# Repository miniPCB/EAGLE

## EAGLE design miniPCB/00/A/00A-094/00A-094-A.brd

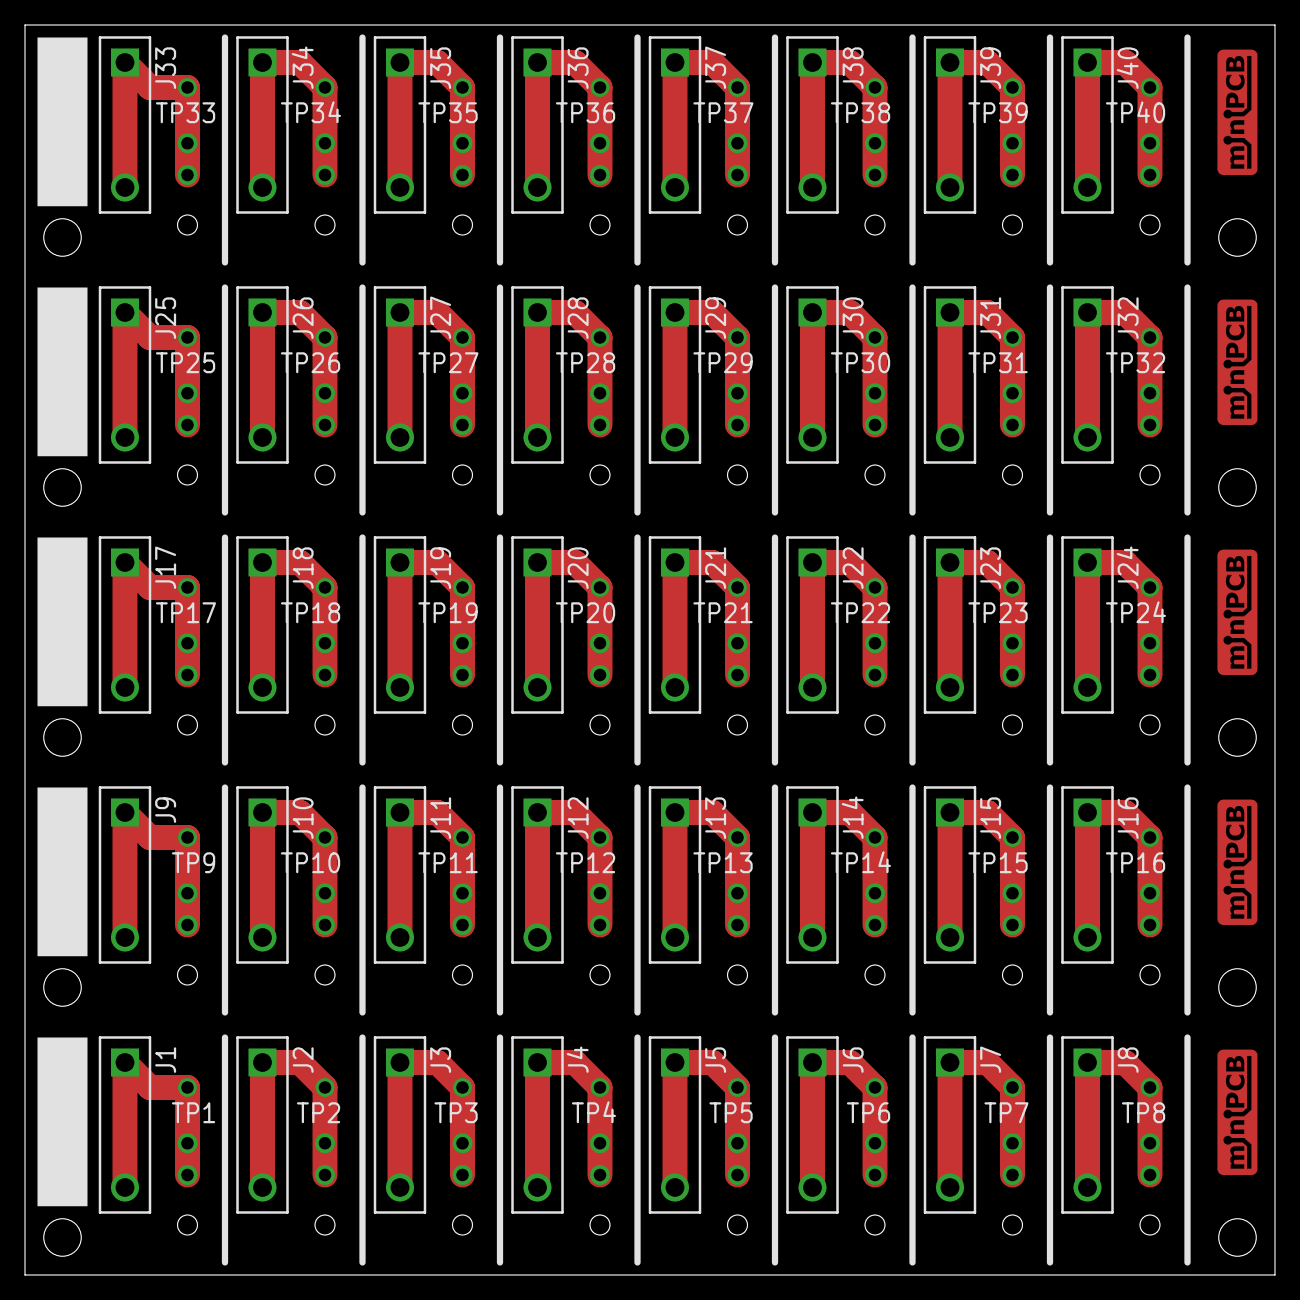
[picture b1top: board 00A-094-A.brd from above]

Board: 2 copper layers, 100.0 x 100.0 mm, 126 parts (0 on the bottom side), 40 nets.

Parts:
E$1: MINIPCB_PANEL_IMAGEFRAME
J1, J2, J3, J4, J5, J6, J7, J8, J9, J10, J11, J12, J13, J14, J15, J16, J17, J18, J19, J20, J21, J22, J23, J24, J25, J26, J27, J28, J29, J30, J31, J32, J33, J34, J35, J36, J37, J38, J39, J40: PINS_1_KE6060
P1, P2, P3, P4, P5, P6, P7, P8, P9, P10, P11, P12, P13, P14, P15, P16, P17, P18, P19, P20, P21, P22, P23, P24, P25, P26, P27, P28, P29, P30, P31, P32, P33, P34, P35, P36, P37, P38, P39, P40: PINS_1_1MM-NOTEXT
PCB1, PCB2, PCB3, PCB4, PCB5: MINIPCB_00A_20X100
TP1, TP2, TP3, TP4, TP5, TP6, TP7, TP8, TP9, TP10, TP11, TP12, TP13, TP14, TP15, TP16, TP17, TP18, TP19, TP20, TP21, TP22, TP23, TP24, TP25, TP26, TP27, TP28, TP29, TP30, TP31, TP32, TP33, TP34, TP35, TP36, TP37, TP38, TP39, TP40: PINS_1_TESTPOINT_KE5000_NOTEXT

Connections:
unnamed: J1.1, J1.2, P1.1, P1.2, TP1.1
unnamed: J8.1, J8.2, P8.1, P8.2, TP8.1
unnamed: J2.1, J2.2, P2.1, P2.2, TP2.1
unnamed: J9.1, J9.2, P9.1, P9.2, TP9.1
unnamed: J3.1, J3.2, P3.1, P3.2, TP3.1
unnamed: J10.1, J10.2, P10.1, P10.2, TP10.1
unnamed: J4.1, J4.2, P4.1, P4.2, TP4.1
unnamed: J11.1, J11.2, P11.1, P11.2, TP11.1
unnamed: J5.1, J5.2, P5.1, P5.2, TP5.1
unnamed: J12.1, J12.2, P12.1, P12.2, TP12.1
unnamed: J6.1, J6.2, P6.1, P6.2, TP6.1
unnamed: J13.1, J13.2, P13.1, P13.2, TP13.1
unnamed: J14.1, J14.2, P14.1, P14.2, TP14.1
unnamed: J7.1, J7.2, P7.1, P7.2, TP7.1
unnamed: J15.1, J15.2, P15.1, P15.2, TP15.1
unnamed: J16.1, J16.2, P16.1, P16.2, TP16.1
unnamed: J17.1, J17.2, P17.1, P17.2, TP17.1
unnamed: J18.1, J18.2, P18.1, P18.2, TP18.1
unnamed: J19.1, J19.2, P19.1, P19.2, TP19.1
unnamed: J20.1, J20.2, P20.1, P20.2, TP20.1
unnamed: J21.1, J21.2, P21.1, P21.2, TP21.1
unnamed: J22.1, J22.2, P22.1, P22.2, TP22.1
unnamed: J23.1, J23.2, P23.1, P23.2, TP23.1
unnamed: J24.1, J24.2, P24.1, P24.2, TP24.1
unnamed: J25.1, J25.2, P25.1, P25.2, TP25.1
unnamed: J26.1, J26.2, P26.1, P26.2, TP26.1
unnamed: J27.1, J27.2, P27.1, P27.2, TP27.1
unnamed: J28.1, J28.2, P28.1, P28.2, TP28.1
unnamed: J29.1, J29.2, P29.1, P29.2, TP29.1
unnamed: J30.1, J30.2, P30.1, P30.2, TP30.1
unnamed: J31.1, J31.2, P31.1, P31.2, TP31.1
unnamed: J32.1, J32.2, P32.1, P32.2, TP32.1
unnamed: J33.1, J33.2, P33.1, P33.2, TP33.1
unnamed: J34.1, J34.2, P34.1, P34.2, TP34.1
unnamed: J35.1, J35.2, P35.1, P35.2, TP35.1
unnamed: J36.1, J36.2, P36.1, P36.2, TP36.1
unnamed: J37.1, J37.2, P37.1, P37.2, TP37.1
unnamed: J38.1, J38.2, P38.1, P38.2, TP38.1
unnamed: J39.1, J39.2, P39.1, P39.2, TP39.1
unnamed: J40.1, J40.2, P40.1, P40.2, TP40.1

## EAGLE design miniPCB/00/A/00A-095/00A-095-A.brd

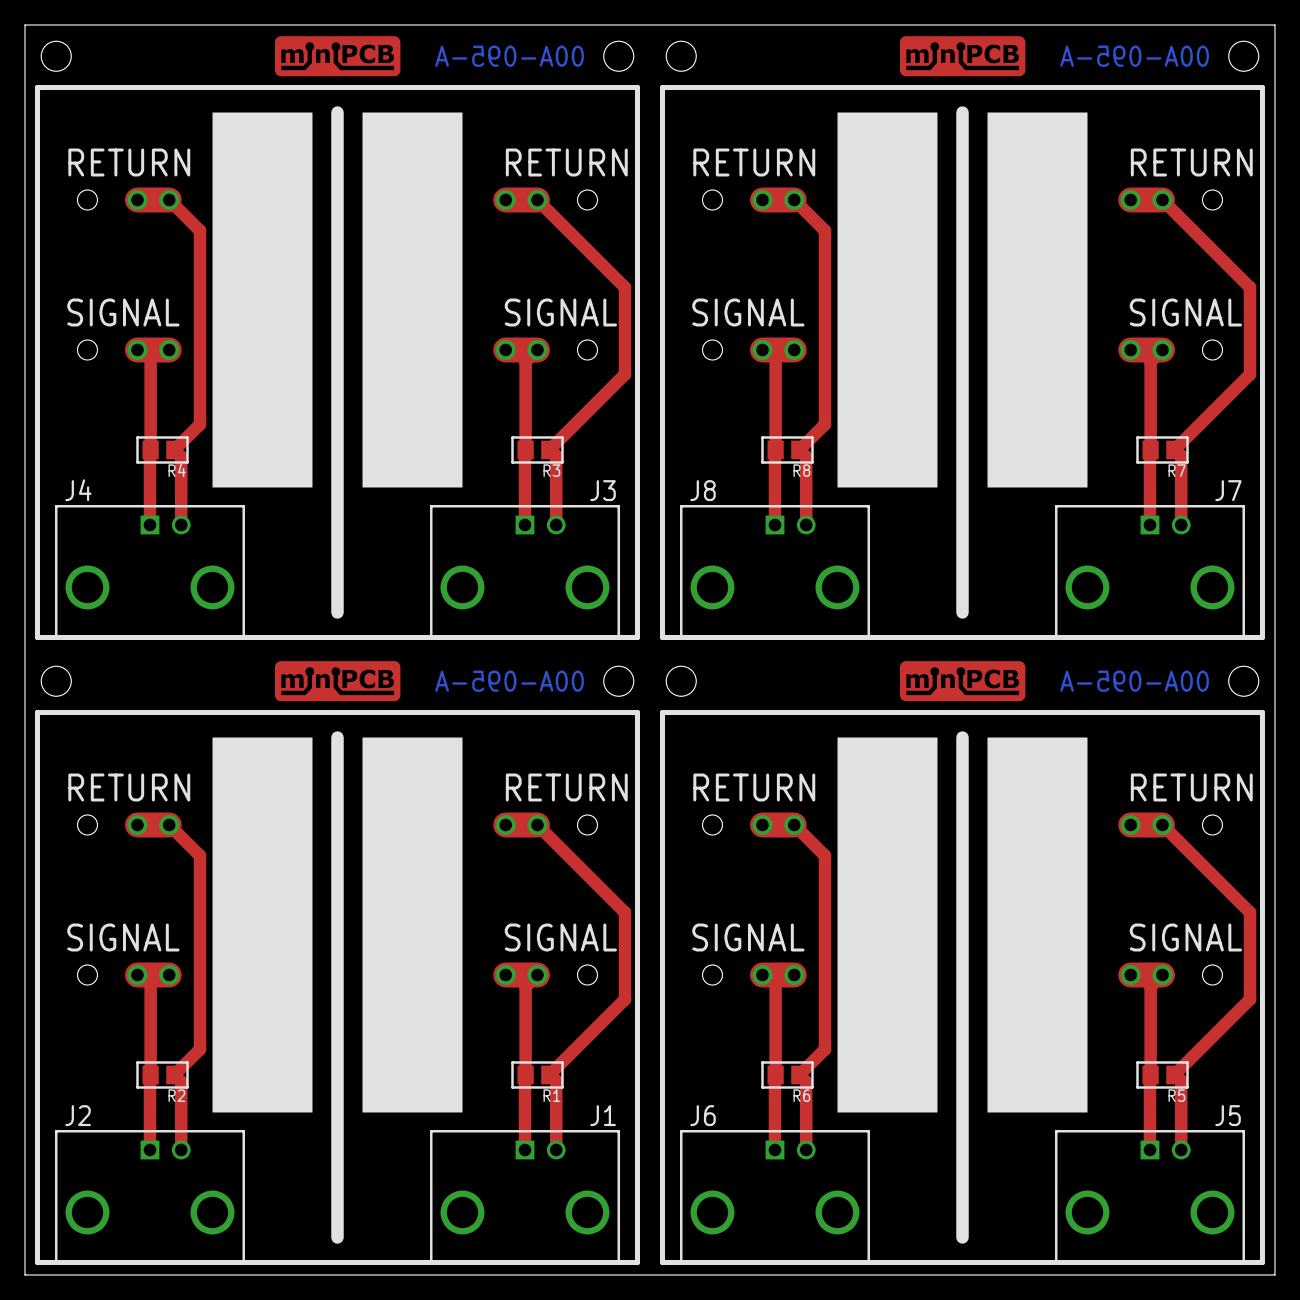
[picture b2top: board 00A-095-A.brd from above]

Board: 2 copper layers, 100.0 x 100.0 mm, 37 parts (0 on the bottom side), 16 nets.

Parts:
E$1: MINIPCB_PANEL_IMAGEFRAME
J1, J2, J3, J4, J5, J6, J7, J8: BNC_RIGHTANGLE
P1, P2, P3, P4, P5, P6, P7, P8, P9, P10, P11, P12, P13, P14, P15, P16: PINS_1_1MM-NOTEXT
PCB1, PCB2, PCB3, PCB4: MINIPCB_0P_50X50MM
R1, R3, R5, R7: 100; R0805
R2, R4, R6, R8: 50; R0805

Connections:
unnamed: J2.1, P3.1, P3.2, R2.2
unnamed: J2.2, P4.1, P4.2, R2.1
unnamed: J1.1, P1.1, P1.2, R1.2
unnamed: J1.2, P2.1, P2.2, R1.1
unnamed: J4.1, P7.1, P7.2, R4.2
unnamed: J4.2, P8.1, P8.2, R4.1
unnamed: J3.1, P5.1, P5.2, R3.2
unnamed: J3.2, P6.1, P6.2, R3.1
unnamed: J6.1, P11.1, P11.2, R6.2
unnamed: J6.2, P12.1, P12.2, R6.1
unnamed: J5.1, P9.1, P9.2, R5.2
unnamed: J5.2, P10.1, P10.2, R5.1
unnamed: J8.1, P15.1, P15.2, R8.2
unnamed: J8.2, P16.1, P16.2, R8.1
unnamed: J7.1, P13.1, P13.2, R7.2
unnamed: J7.2, P14.1, P14.2, R7.1

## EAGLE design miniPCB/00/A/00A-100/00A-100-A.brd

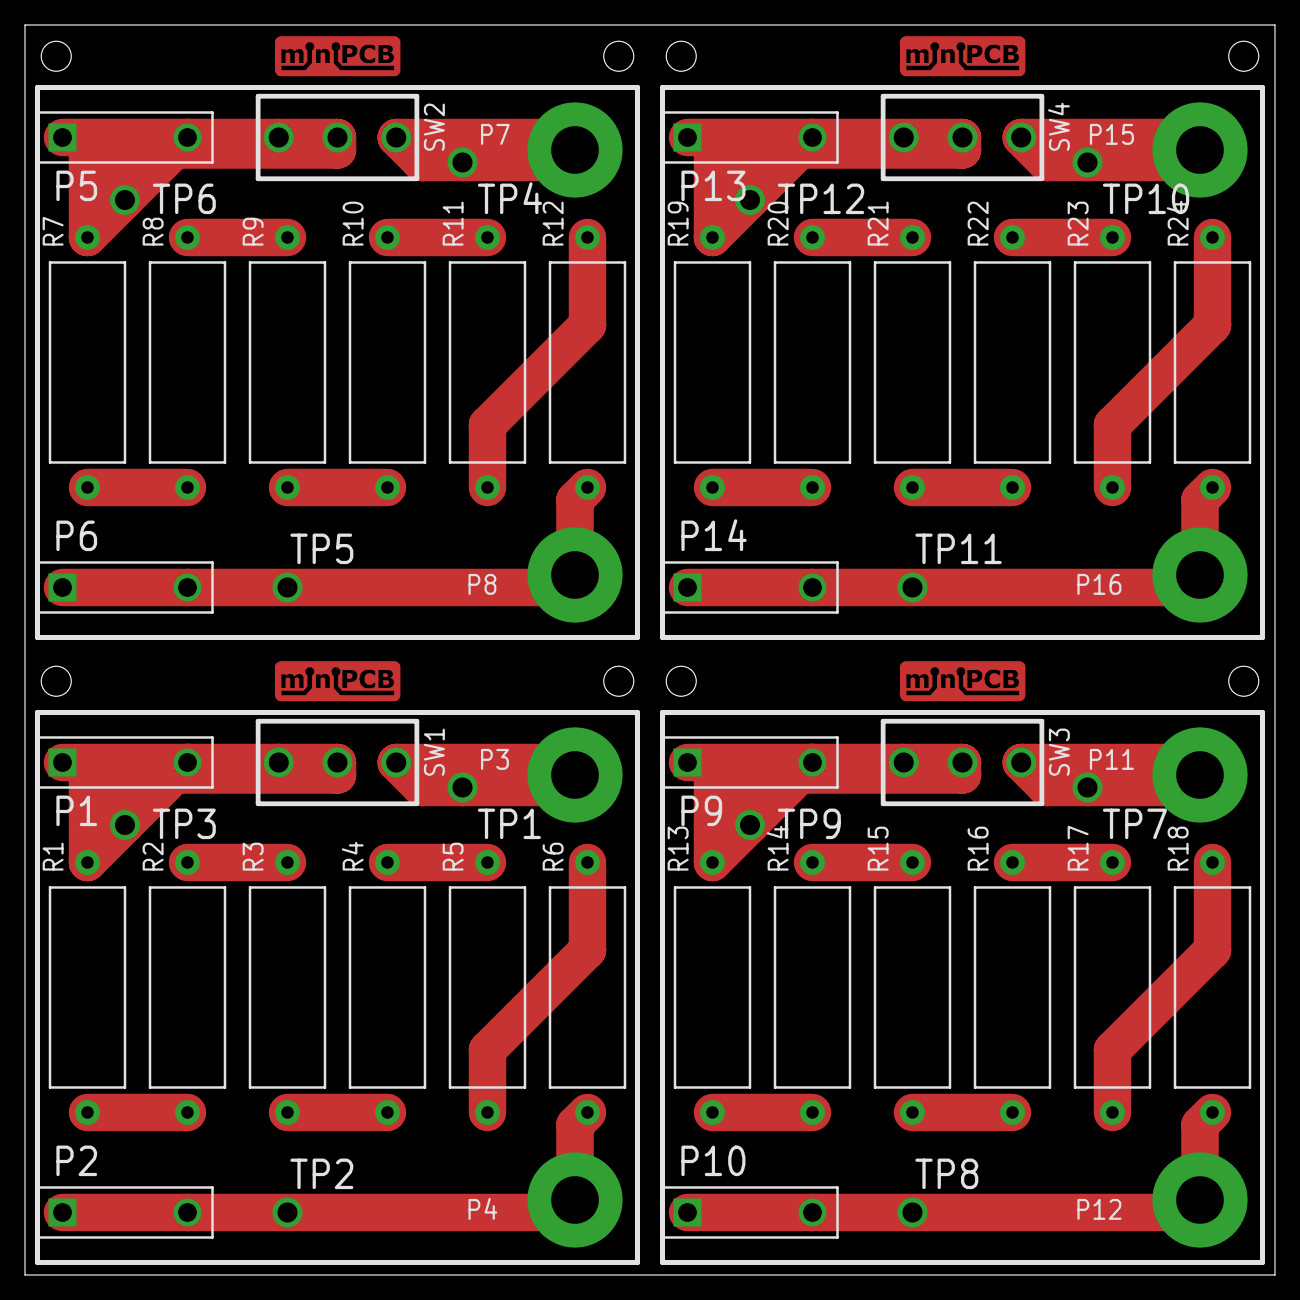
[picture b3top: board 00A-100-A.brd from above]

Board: 2 copper layers, 100.0 x 100.0 mm, 61 parts (0 on the bottom side), 32 nets.

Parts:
E$1: MINIPCB_PANEL_IMAGEFRAME
P1, P2, P5, P6, P9, P10, P13, P14: PINS_1_KE6060
P3, P4, P7, P8, P11, P12, P15, P16: BANANAPOST
PCB1, PCB2, PCB3, PCB4: MINIPCB_0P_50X50MM
R1, R2, R3, R4, R5, R6, R7, R8, R9, R10, R11, R12, R13, R14, R15, R16, R17, R18, R19, R20, R21, R22, R23, R24: R-THD-15MM
SW1, SW2, SW3, SW4: CK1101
TP1, TP2, TP3, TP4, TP5, TP6, TP7, TP8, TP9, TP10, TP11, TP12: PINS_1_TESTPOINT_KE5100

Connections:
unnamed: P1.1, P1.2, R1.1, SW1.P$2, SW1.P$3, TP3.1
unnamed: P2.1, P2.2, P4.1, R6.1, TP2.1
unnamed: R1.2, R2.1
unnamed: R2.2, R3.1
unnamed: P3.1, SW1.P$1, TP1.1
unnamed: R3.2, R4.2
unnamed: R4.1, R5.2
unnamed: R5.1, R6.2
unnamed: P5.1, P5.2, R7.1, SW2.P$2, SW2.P$3, TP6.1
unnamed: P6.1, P6.2, P8.1, R12.1, TP5.1
unnamed: R7.2, R8.1
unnamed: R8.2, R9.1
unnamed: P7.1, SW2.P$1, TP4.1
unnamed: R9.2, R10.2
unnamed: R10.1, R11.2
unnamed: R11.1, R12.2
unnamed: P9.1, P9.2, R13.1, SW3.P$2, SW3.P$3, TP9.1
unnamed: P10.1, P10.2, P12.1, R18.1, TP8.1
unnamed: R13.2, R14.1
unnamed: R14.2, R15.1
unnamed: P11.1, SW3.P$1, TP7.1
unnamed: R15.2, R16.2
unnamed: R16.1, R17.2
unnamed: R17.1, R18.2
unnamed: P13.1, P13.2, R19.1, SW4.P$2, SW4.P$3, TP12.1
unnamed: P14.1, P14.2, P16.1, R24.1, TP11.1
unnamed: R19.2, R20.1
unnamed: R20.2, R21.1
unnamed: P15.1, SW4.P$1, TP10.1
unnamed: R21.2, R22.2
unnamed: R22.1, R23.2
unnamed: R23.1, R24.2

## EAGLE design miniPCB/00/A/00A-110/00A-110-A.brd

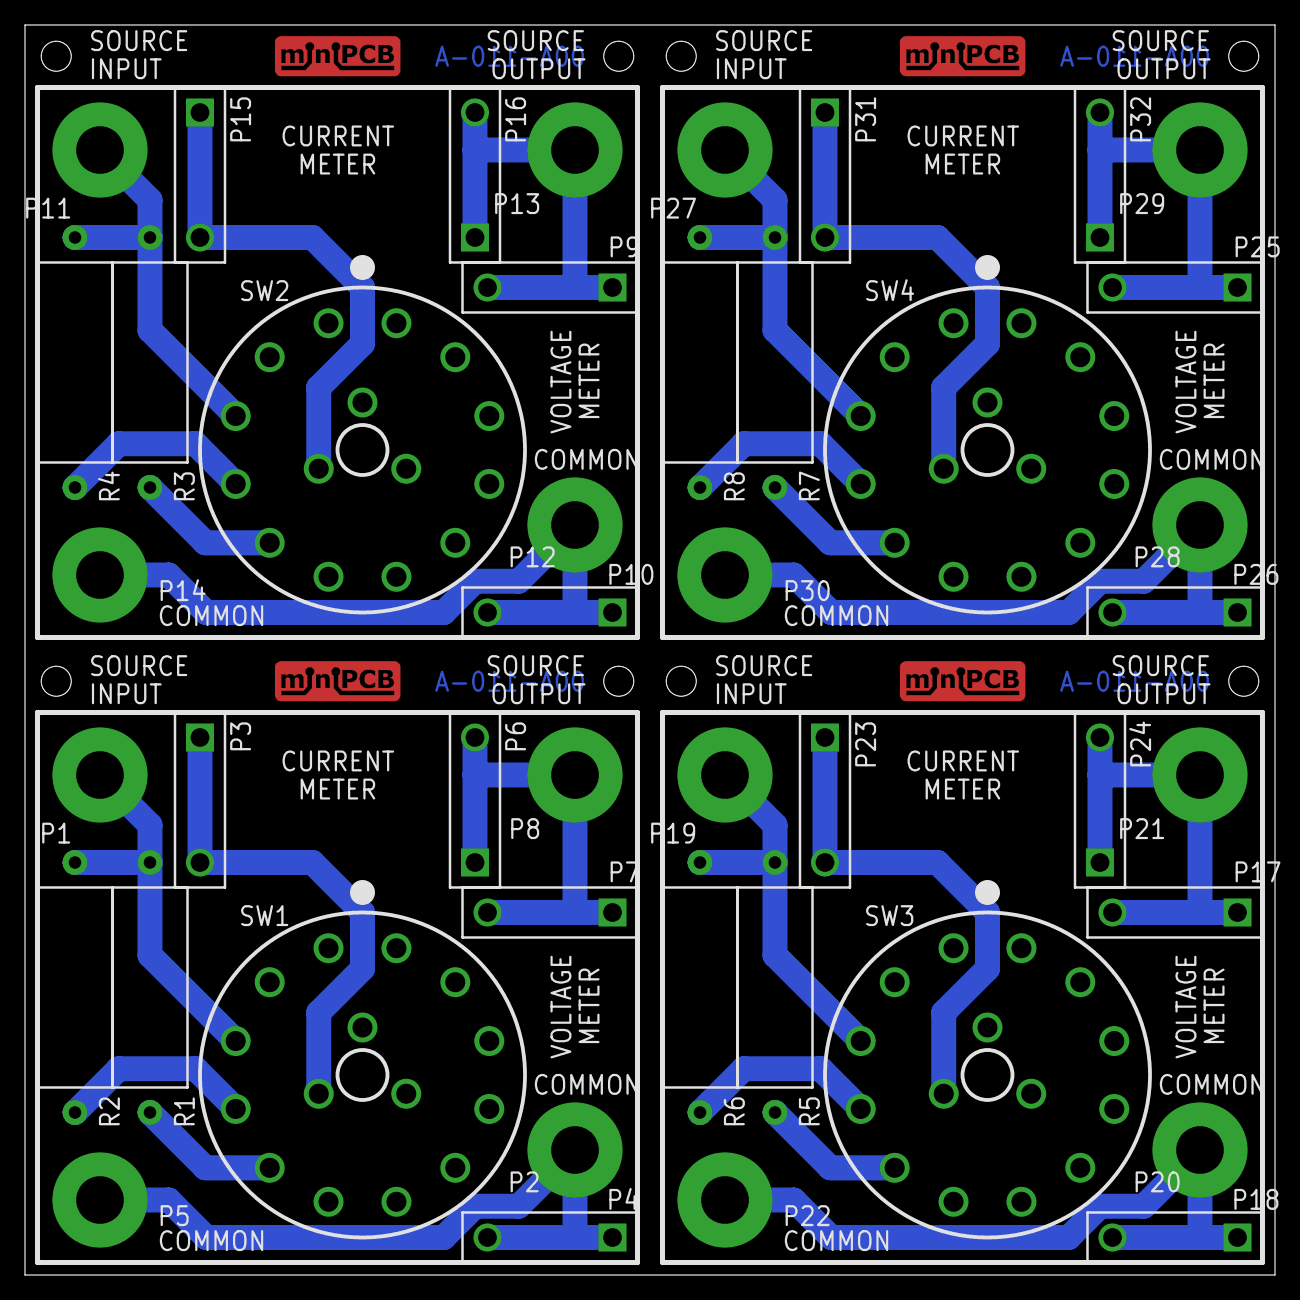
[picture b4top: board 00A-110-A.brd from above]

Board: 2 copper layers, 100.0 x 100.0 mm, 49 parts (0 on the bottom side), 24 nets.

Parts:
E$1: MINIPCB_PANEL_IMAGEFRAME
P1, P2, P5, P8, P11, P12, P13, P14, P19, P20, P21, P22, P27, P28, P29, P30: BANANAPOST
P3, P4, P6, P7, P9, P10, P15, P16, P17, P18, P23, P24, P25, P26, P31, P32: PINS_1_KE6060
PCB1, PCB2, PCB3, PCB4: MINIPCB_0P_50X50MM
R1, R3, R5, R7: 100; R-THD-15MM
R2, R4, R6, R8: 50; R-THD-15MM
SW1, SW2, SW3, SW4: SWITCH-ROTARY-3P4T

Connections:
unnamed: P2.1, P4.1, P4.2, P5.1
unnamed: P1.1, R1.1, R2.1, SW1.4
unnamed: R1.2, SW1.2
unnamed: R2.2, SW1.3
unnamed: P6.1, P6.2, P7.1, P7.2, P8.1
unnamed: P3.1, P3.2, SW1.A
unnamed: P10.1, P10.2, P12.1, P14.1
unnamed: P11.1, R3.1, R4.1, SW2.4
unnamed: R3.2, SW2.2
unnamed: R4.2, SW2.3
unnamed: P9.1, P9.2, P13.1, P16.1, P16.2
unnamed: P15.1, P15.2, SW2.A
unnamed: P18.1, P18.2, P20.1, P22.1
unnamed: P19.1, R5.1, R6.1, SW3.4
unnamed: R5.2, SW3.2
unnamed: R6.2, SW3.3
unnamed: P17.1, P17.2, P21.1, P24.1, P24.2
unnamed: P23.1, P23.2, SW3.A
unnamed: P26.1, P26.2, P28.1, P30.1
unnamed: P27.1, R7.1, R8.1, SW4.4
unnamed: R7.2, SW4.2
unnamed: R8.2, SW4.3
unnamed: P25.1, P25.2, P29.1, P32.1, P32.2
unnamed: P31.1, P31.2, SW4.A
